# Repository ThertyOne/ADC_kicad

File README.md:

# mini-project ADC

## Opis projektu
Projekt przedstawia układ do precyzyjnej konwersji analogowo-cyfrowej oparty na przetworniku ADC ADS8881, wspomaganym przez wzmacniacze operacyjne oraz stabilizatory napięcia. Układ został zoptymalizowany względem poprzedniej wersji, uwzględniając poprawki dotyczące źródła napięcia referencyjnego, filtracji sygnału wejściowego oraz zasilania.

## Zmiany względem poprzedniej wersji
1. **Implementacja układu z rysunku 70 z dokumentacji ADS8881** – poprawiona konfiguracja układu przetwornika ADC.
2. **Napięcie referencyjne** pochodzi teraz ze stabilizatora LDO, które również zasila wzmacniacze operacyjne w układzie. Napięcie wejściowe wynosi 12V.
3. **Filtr wejściowy** został poprawiony – zastosowano górnoprzepustowy filtr o częstotliwości odcięcia **48 Hz**.
4. **Dodano stabilizator napięcia 3V**, który zasila przetwornik ADS8881, zgodnie z jego specyfikacją (dopuszczalne napięcie zasilania od 2.7V do 3.6V).

## Kluczowe elementy układu
- **Mikrokontroler**: Raspberry Pi Pico – sterowanie przetwornikiem ADC.
- **Przetwornik ADC**: ADS8881 – 18-bitowy, szybki i precyzyjny konwerter analogowo-cyfrowy.
- **Stabilizatory napięcia**:
  - **TPS7A49** – stabilizator napięcia referencyjnego.
  - **LM4040** – dodatkowe źródło referencyjne 3V dla ADS8881.
- **Wzmacniacze operacyjne**:
  - **OPA320** – wzmacniacz buforujący sygnał wejściowy.
  - **THS4521** – różnicowy wzmacniacz sygnału dla przetwornika ADC.

## Power Supply (LDO)
Układ zawiera kilka wzmacniaczy operacyjnych, które wymagają stabilnego zasilania. Wybrano zasilanie 5V, ponieważ wszystkie użyte wzmacniacze operacyjne mogą pracować przy tym napięciu. Stabilizator niskoszumowy (LDO) **TPS7A49** został wybrany ze względu na swoje niskie szumy (15,4 µV RMS) oraz prostą konfigurację napięcia wyjściowego przy użyciu jedynie dwóch rezystorów. Dodatkowo zastosowano diodę TVS do ochrony układu przed przepięciami oraz wskaźnik napięcia wyjściowego 5V.

## LM4040 Voltage Reference
Aby zasilić zarówno sekcję analogową, jak i cyfrową przetwornika **ADS8881** (który działa w zakresie 2,7V - 3,6V), użyto stabilizatora **LM4040**, który konwertuje 5V z LDO na 3V dla ADC. Dzięki temu poziomy logiczne na wyjściu ADC będą miały maksymalne napięcie 3V, co nie stanowi problemu dla **Raspberry Pi Pico**, gdyż powinien on niezawodnie rozpoznawać 2,7V jako wysoki poziom logiczny.

## Input Signal Processing
Sygnał wejściowy z fotodiody przechodzi przez filtr górnoprzepustowy **50 Hz**, a następnie przez wzmacniacz, który wzmacnia sygnał i izoluje go od obciążenia.

## Analog-to-Digital Conversion (ADC)
Zgodnie z zaleceniami z poprzedniego maila wdrożono konfigurację **ADS8881** zgodnie z **rysunkiem 70** z dokumentacji. Konfiguracja ta jest zasilana **5V z LDO**, które jednocześnie pełni rolę napięcia referencyjnego dla ADC. Jak wspomniano wcześniej, sam ADC jest zasilany napięciem **3V ze stabilizatora LM4040**, a obie sekcje – analogowa i cyfrowa – są wyposażone w **kondensatory odsprzęgające 1µF**. Linie komunikacyjne są podłączone do **Raspberry Pi Pico**, które odpowiada wyłącznie za wyzwalanie pomiaru i odczyt danych z ADC.

## Schemat
Projekt został opracowany w **KiCad** i zapisany w pliku `adc.kicad_sch`. Schemat zawiera podział na bloki funkcjonalne:
- Stabilizacja napięcia (LDO, stabilizator 3V)
- Filtracja sygnału wejściowego (filtr górnoprzepustowy)
- Konwersja analogowo-cyfrowa (ADS8881 + wzmacniacze operacyjne)
- Sterowanie i komunikacja z mikrokontrolerem

## Wymagane napięcia
- **Vin**: 12V
- **Vref**: 5V (ze stabilizatora LDO)
- **Zasilanie ADC**: 3V

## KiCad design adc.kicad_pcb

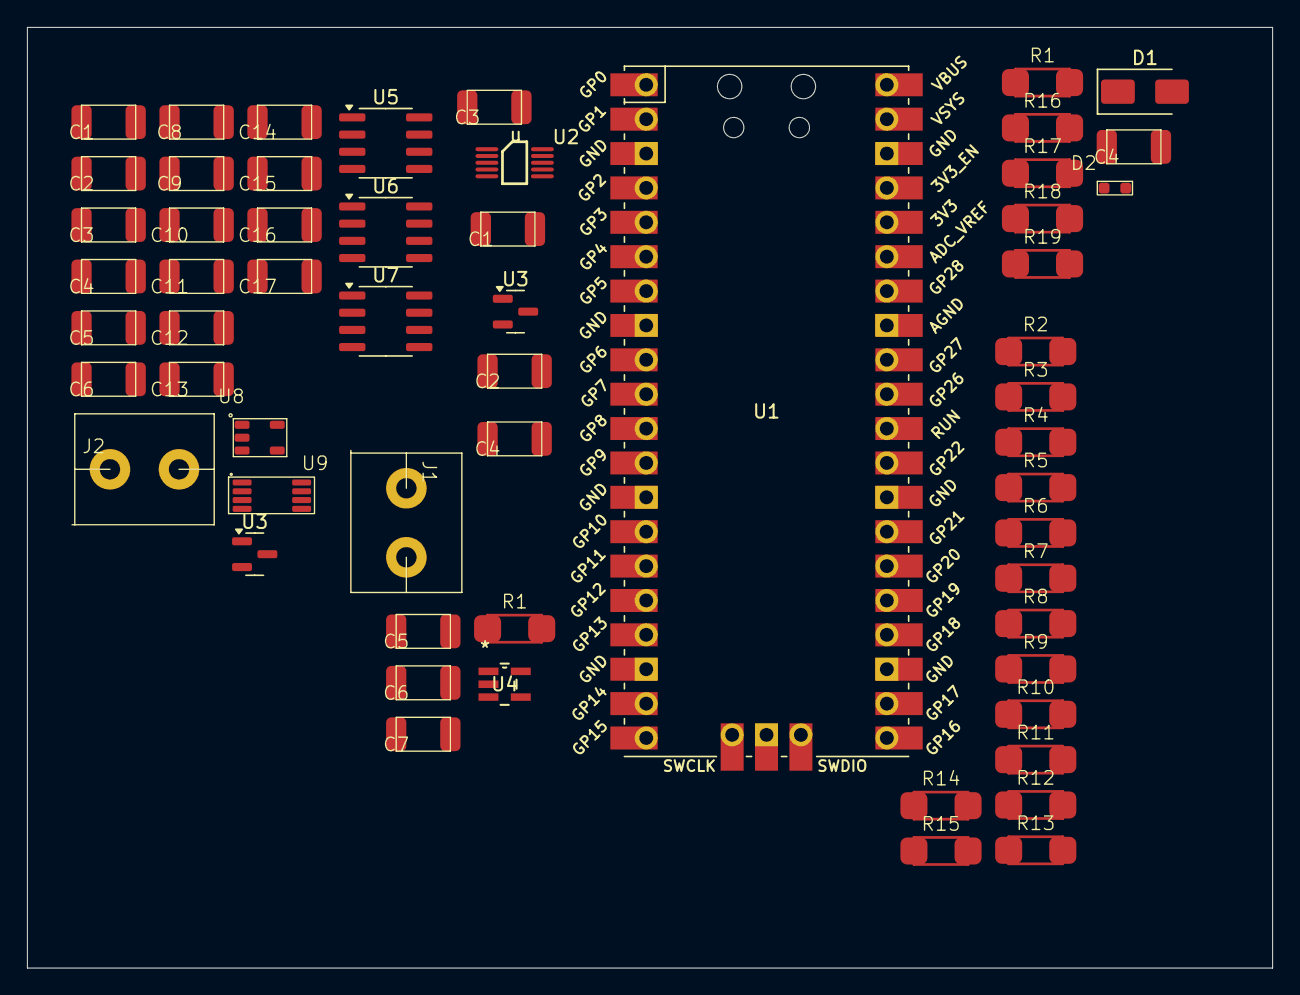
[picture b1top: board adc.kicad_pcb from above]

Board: 2 copper layers, 92.0 x 69.5 mm, 58 parts (0 on the bottom side), 32 nets, no tracks yet.

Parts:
C1, C2, C3, C3#2, C4#2, C6, C12, C13: 1u; cap_1206
C1#2, C4, C5#2, C6#2, C11, C14, C17: 10u; cap_1206
C2#2, C5, C9, C10: 100n; cap_1206
C4#3, C7: 33u; cap_1206
C8, C15, C16: 10n; cap_1206
D1: SMAJ12A; D_SMA
D2: LED; LED_SMD
J1, J2: Screw_Terminal_01x02; screw_conector
R1, R1#2, R14, R19: 100; res_1206
R2, R4, R8, R9, R10, R11, R13: 1k; res_1206
R3: 0.2; res_1206
R5: 20k; res_1206
R6, R7: 10; res_1206
R12: 4.7k; res_1206
R15, R18: 10k; res_1206
R16: 400; res_1206
R17: 470; res_1206
U1: Pico; RPi_Pico_SMD_TH
U2: ADS8881CDGS; ADS8881
U3, U3#2: LM4040DBZ-3; SOT-23
U4: OPA320AIDBVR; DBV5
U5: THS4521ID; SOIC-8_3.9x4.9mm_P1.27mm
U6: OPA333xxD; SOIC-8_3.9x4.9mm_P1.27mm
U7: REF5045AD; SOIC-8_3.9x4.9mm_P1.27mm
U8: THS4281
U9: TPS7A49

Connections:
3.3V: C1#2.1, C2#2.1, C3#2.1, C4#2.1, C5.1, C6#2.1, U1.36 (3V3), U3.1 (K)
+3: C4.1, C9.1, C10.1, C11.1, C12.1, C13.1, R16.2, U2.2 (AVDD), U2.10 (DVDD), U3#2.1 (K)
+5: C16.1, C17.1, D2.2 (A), R12.1, R14.1, R16.1, U4.5 (V+), U5.3 (V_{S+}), U5.7 (~PD), U6.7 (V+), U7.2 (Vin), U8.5 (V+), U9.1 (OUT)
CONVS: U1.2 (GPIO1), U2.6 (CONVST)
DIN: U1.5 (GPIO3), U2.9 (DIN)
DIODE_IN: C7.2, R1#2.1
DIODE_SIGNAL: R11.2, R18.1, U4.1
DOUT: U1.1 (GPIO0), U2.7 (DOUT)
GND: C1#2.2, C2.2, C2#2.2, C3.2, C3#2.2, C4.2, C4#2.2, C5.2, C5#2.2, C6.2, C6#2.2, C9.2, C10.2, C11.2, C12.2, C13.2, C14.2, C15.2, C17.2, D1.2 (A2), J1.2, J2.2, R1.2, R1#2.2, R9.1, R13.2, R17.2, R19.2, U1.28 (GND), U1.42 (GND), U2.5 (GND), U3.2 (A), U3#2.2 (A), U4.2 (V-), U5.6 (V_{S-}), U6.4 (V-), U7.4 (GND), U8.2 (V-), U9.4 (GND)
unnamed: C1.1, R4.1, U6.6
unnamed: C5#2.1, R3.2
unnamed: C14.1, D1.1 (A1), J2.1, U9.5 (EN), U9.8 (IN)
unnamed: D2.1 (K), R17.1
unnamed: C4#3.1, J1.1
unnamed: R7.2, R8.1, U5.4
unnamed: R6.2, R10.1, U5.5
unnamed: R14.2, R15.1
unnamed: C8.2, R7.1, U2.4 (AINM)
unnamed: C8.1, R6.1, U2.3 (AINP)
unnamed: C4#3.2, R1.1, U4.3 (+)
unnamed: R18.2, R19.1, U4.4 (-)
unnamed: R10.2, R11.1, U5.8 (+)
unnamed: R8.2, R9.2, U5.1 (-)
unnamed: C6.1, R2.2, U6.3 (+)
unnamed: C1.2, R5.1, U6.2 (-)
unnamed: C3.1, U7.5 (Trim/NR)
unnamed: R2.1, U7.6 (Vout)
unnamed: C2.1, R4.2, U8.3 (+)
unnamed: C16.2, R12.2, R13.1, R15.2, U9.2 (FB)
unnamed: C15.1, U9.6 (NE/SS)
SCLK: U1.4 (GPIO2), U2.8 (SCLK)
V_REF: R3.1, R5.2, U2.1 (REF), U5.2 (V_{OCM}), U8.1, U8.4 (-)

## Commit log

2025-02-06 opis
